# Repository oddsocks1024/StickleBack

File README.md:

# Stickleback

## Description
A clone of the First Byte Joystick Interface with audio out and pass-through for the Acorn Electron, that connects to the rear expansion connector

**Features**
* 9-pin standard Atari-type digital joystick connector
* Compatible with the First Byte Switched Joystick Interface
  * Compatible with games that include native First Byte support
  * Compatible with most keyboard only games (via FB utility)
  * Compatible with most analogue joystick games (via FB utility)
* 3.5mm Audio Out Jack (externally amplified devices only)
* Pass-through connector
* Power LED

**Compatible Joysticks**

Any DE9 (9pin) digital joystick or joypad that uses the 'Atari' single button standard. This standard was very common on many computers and
consoles of the era and was not exclusive to Atari systems. For example joysticks which claim they are compatible with Atari Systems, C64, Amiga, VIC-20,
Kempston and others should work fine.

**Incompatible Joystick Standards**

Although these joysticks standards use the same DE9 connector, they use incompatible signalling and should not be used with the Stickleback

| Incompatible Standards |
|------------------------|
| 3D0                    |
| Interface II           |
| J-PC                   |
| MSX                    |
| SEGA                   |
| Sinclair               |
| X68000                 |

## Bill of Materials

| Qty | Component                                 |
|:---:|-------------------------------------------|
| 1   | 5mm LED                                   |
| 1   | 330Ω Axial Resistor - ¼ watt (LED)        |
| 4   | 10KΩ Axial Resistors - ¼ watt             |
| 1   | 74LS138 16pin DIP                         |
| 1   | 74LS367 16pin DIP                         |
| 1   | 74LS30 14pin DIP                          |
| 1   | 10uF Radial Electrolytic Capacitor        |
| 1   | 5-pin 3.5mm Audio Jack Socket TN/T/RN/R/S |
| 1   | Male DE-9 Connector - right angled        |
| 1   | 50pin (2x25) Edge Connector               |

* IC sockets optional
* The LED resistor is nominally 330Ω but anything up to 1K is fine
* The 3.5mm jack audio socket footprint is for a 5pin TN/T/RN/R/S connector
  * If you do not care about audio, you can omit the audio socket and the 10uF capacitor entirely.
  * As the audio is mono and no switching is enabled, TN/T/RN/R are all wired together.
  * This means should be compatible with several other 3.5mm jack socket types. 

## 3D Printable Case
A 3D printable case specifically designed for this PCB is also available. STLs are included in this repo and there is also a [Thingiverse Page](https://www.thingiverse.com/thing:7089362)

* Designed to use screws as they produce a much nicer, more robust case
* 4 x 3.5mm self-tapping screws to attach the shells. Max length about 15mm

---

## Usage
The Stickleback has several modes of operation which allow the Joystick to be used with almost every Acorn Electron game.

### Native Mode
Native mode means the game has built-in support for this joystick interface and no further setup is required. This joystick interface is referred to by several names as shown
in the table

| Name                 |
|----------------------|
| First Byte Interface |
| FB Interface         |
| FCC0 Interface       |

In cases where a game requests joystick configuration values, use these values

| Parameter  | Value |
|------------|:-----:|
| Address    | FCC0  |
| Code Type  | 1     |

Examples of games with native support

| Game           |
|----------------|
| CRACK-UP       |
| FRAK!          |
| HOSTAGES       |
| RUBBLE TROUBLE |

### Keyboard Emulation Mode
This mode is used for games that have no joystick support at all. A small software routine is installed which makes the joystick emulate
key presses. See the software section for more information.

### Analogue Emulation Mode
This mode is used for games that only support Acorn's Analogue Joystick. A small software routine is installed which makes the joystick simulate
the Acorn Analogue Joystick. See the software section for more information.

### Audio
* The Stickleback provides an audio out connecting using a 3.5mm jack socket. Any audio device connected **MUST** be externally amplified
* When an external audio device is connected, the Electron's internal speaker will still produce sound. If this is not desired you can open the case and simply disconnect the internal speaker

## Software
There are some cassette tape and disc images available in the repo which contain software utilities to support the First Byte (and consequently the Stickleback) joystick interface.

### STICKLE
Available on the disc image. Test the joystick by moving a little stickleback. Very simple, only - up, down, left, right and fire.

```
   10 REM STICKLEBACK JOYSTICK TEST
   20 MODE 5
   30 VDU 23,1,0;0;0;0
   40 CLS
   50 VDU 23,240,6,12,62,127,223,255,127,62
   60 VDU 23,241,0,0,48,96,224,192,96,48
   70 X=10:Y=10
   80 COLOUR 2
   90 PRINT "STICKLEBACK JOYSTICK"
  100 PRINT TAB(X,Y);CHR$(240)+CHR$(241)
  110 F% = 0
  120 J% = ?&FCC0 AND 32
  130 IF J% <> 32 THEN F%=1
  140 J% = 31 AND ?&FCC0
  150 IF F% = 1 THEN J% = 31 - J% 
  160 IF J% > 14 AND J% < 31 THEN PRINT TAB(X,Y);"  "
  170 IF J% = 30 AND Y > 1 THEN Y = Y - 1
  180 IF J% = 29 AND Y < 29 THEN Y = Y + 1
  190 IF J% = 27 AND X > 1 THEN X = X - 1
  200 IF J% = 23 AND X < 18  THEN X = X + 1
  210 IF J% = 15 THEN SOUND 12,12,12,12
  220 GOTO 100
```

### JOYTST
Available on the disc image. The original First Byte test program which also prints the the direction values for use in BASIC
```
   10 FLAG% = 0
   20 JOY% = ?&FCC0 AND 32
   30 IF JOY% <> 32 THEN FLAG% = 1
   40 JOY% = 31 AND ?&FCC0 
   50 IF FLAG% = 1 THEN JOY% = 31 - JOY%
   60 PRINT JOY%
   70 GOTO 40

```

### JoyGame
This is the "First Byte Joystick Interface" games menu which can be loaded from the cassette or disc image. It essentially contains a list of games which are automatically "patched" to add
support for the joystick. Choose the game and then continue to load the game from cassette or disc.

| Games Menu                 |
|----------------------------|
| SNAPPER                    |
| ARCADE                     |
| FREE FALL                  |
| STARSHIP COMMAND           |
| HOPPER                     |
| MONSTERS                   |
| METEORS                    |
| MOONRAIDER                 |
| CYBERTRON MISSION          |
| SWOOP                      |
| KILLER GORILLA             | 
| CROAKER                    |
| ESCAPE FROM MOONBASE ALPHA |
| BANDITS AT 3 O'CLOCK       |
| POSITRON                   |
| ELECTRON INVADERS          | 
| GALACTIC COMMANDER         | 
| GISBURNE'S CASTLE          | 
| MR WIZ                     |
| ALIEN DROPOUT              | 
| CHUCKIE EGG                |
| KAMIKAZE                   |
| SPACE STATION ALPHA        | 
| VORTEX                     |
| DIAMOND MINE               | 
| ALIEN BREAK IN             |
| BIRDS OF PREY              | 
| ATOM SMASHER               |
| DYNABYTE POOL              | 
| BLAGGER                    |
| BUGBLASTER                 |
| LUNAR RESCUE               |
| GUARDIAN                   |
| CITY DEFENCE               |
| GALAXY WARS                |
| PENGWYN                    |
| HUNCHBACK                  |

**Cassette Loading**
 - Insert the JoyGame cassette
 - `*TAPE`
 - `CHAIN ""`
 - Choose your game from the menu
 - Insert your game cassette
 - `CHAIN ""`

**Disc Loading**
 - Insert the JoyUtils disc
  - `*DISC`
 - `CHAIN "JOYGAME"`
 - Choose your game from the menu
 - Insert your game disc
 - `*EXEC !BOOT` (do not use SHIFT+BREAK to boot)

### JoyPch
This is the "First Byte Joystick Interface" setup menu which can be loaded from the cassette or disc image. It essentially allows you to patch any game for use with the joystick. There are two analogue routines which work
with games that support analogue joysticks. The only difference between the routines is the addresses that they sit at. The last option is for keyboard emulation. You can
define the keys that the joystick will emulate then load the game.

**Cassette Loading**
 - Insert the JoyPch cassette
 - `*TAPE`
 - `CHAIN ""`
 - Choose the routine to use
 - Insert your game cassette
 - `CHAIN ""`

**Disc Loading**
 - Insert the JoyUtils disc
 - `*DISC`
 - `CHAIN "JOYPCH"`
 - Choose the routine to use
 - Insert your game disc
 - `*EXEC !BOOT` (do not use SHIFT+BREAK to boot)

## Support Me
* [My Projects](https://projects.amiga-hardware.com) - Donate on this page
* [Order the Stickleback PCB](https://www.pcbway.com/project/shareproject/StickleBack_Acorn_Electron_Joystick_Interface_Audio_Out_49529ca6.html)
* [Order the Stickleback Case](https://www.pcbway.com/project/shareproject/StickleBack_Acorn_Electron_Joystick_Interface_Case_1205cf12.html)

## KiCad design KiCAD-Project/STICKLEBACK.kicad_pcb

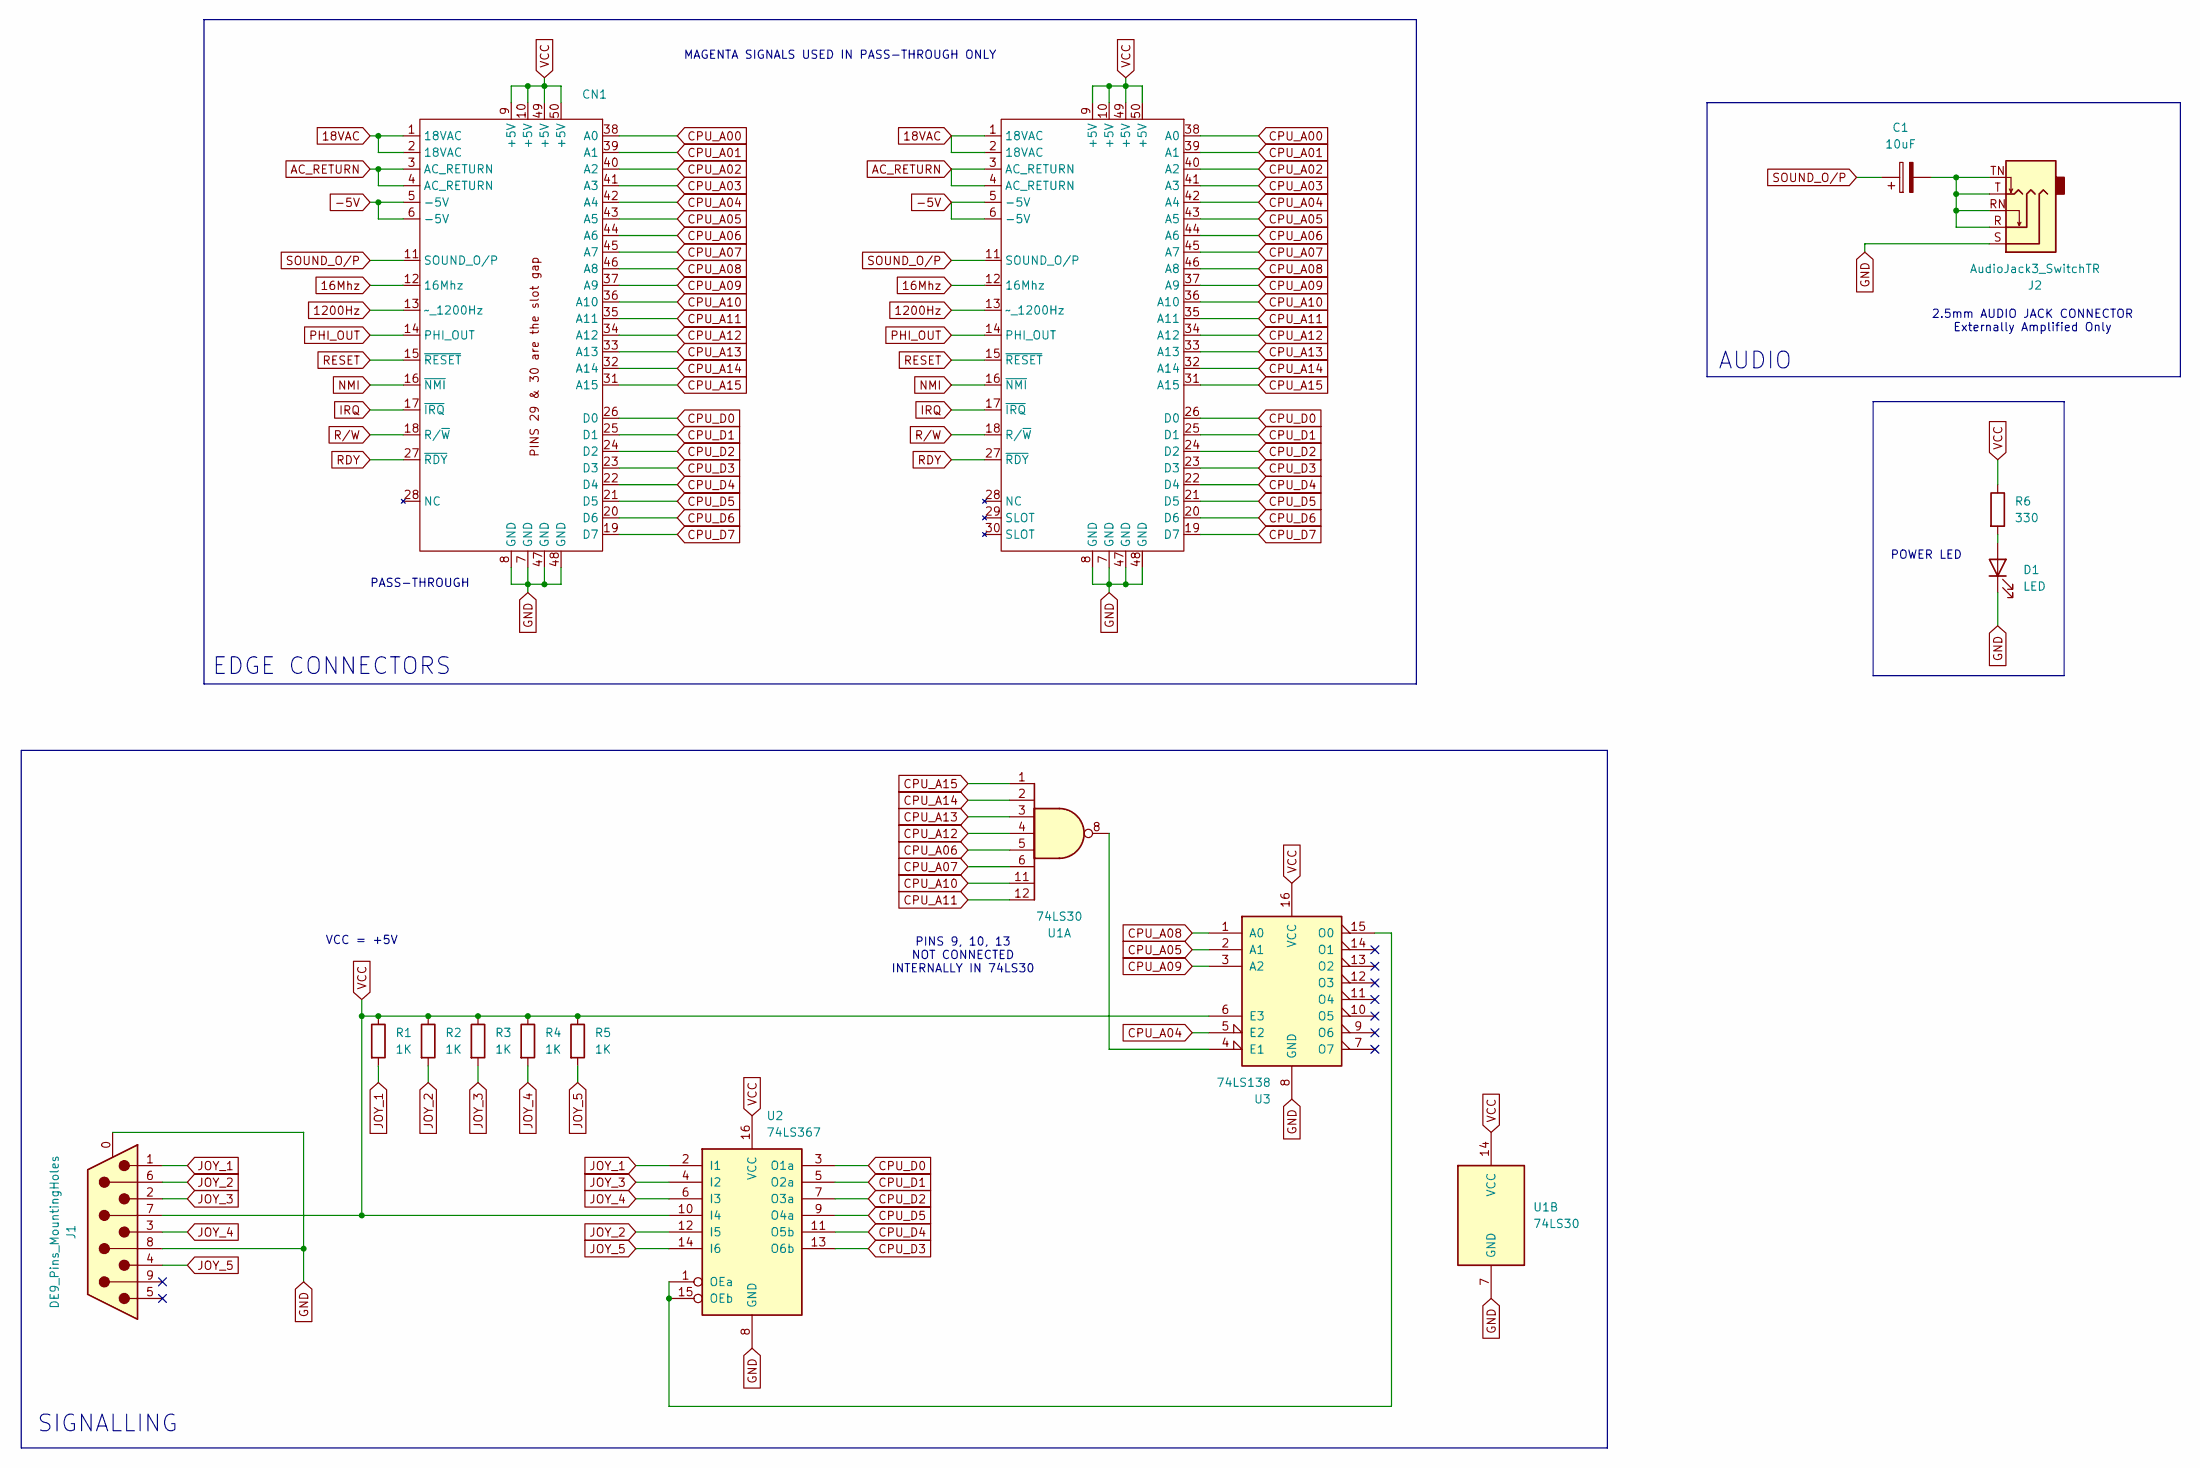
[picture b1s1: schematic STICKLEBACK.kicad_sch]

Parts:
C1: 10uF; CP_Radial_D5.0mm_P2.50mm
CN1: Acorn Electron Expansion Edge Connector
CN2: Acorn Electron TE 5530843-5 PADS
D1: LED; LED_D5.0mm
J1: DE9_Pins_MountingHoles; DSUB-9_Pins_Horizontal_P2.77x2.84mm_EdgePinOffset14.56mm_Ho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
J2: AudioJack3_SwitchTR; Jack_3.5mm_CUI_SJ1-3525N_Horizontal
R1, R2, R3, R4, R5: 1K; R_Axial_DIN0207_L6.3mm_D2.5mm_P10.16mm_Horizontal
R6: 330; R_Axial_DIN0207_L6.3mm_D2.5mm_P10.16mm_Horizontal
U1: 74LS30; DIP-14_W7.62mm_Socket
U2: 74LS367; DIP-16_W7.62mm_Socket
U3: 74LS138; DIP-16_W7.62mm_Socket

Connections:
16Mhz: CN1.12 (16Mhz), CN2.12 (16Mhz)
18VAC: CN1.1 (18VAC), CN1.2 (18VAC), CN2.1 (18VAC), CN2.2 (18VAC)
1200Hz: CN1.13 (~_1200Hz), CN2.13 (~_1200Hz)
-5V: CN1.5 (-5V), CN1.6 (-5V), CN2.5 (-5V), CN2.6 (-5V)
AC_RETURN: CN1.3 (AC_RETURN), CN1.4 (AC_RETURN), CN2.3 (AC_RETURN), CN2.4 (AC_RETURN)
CPU_A00: CN1.38 (A0), CN2.38 (A0)
CPU_A01: CN1.39 (A1), CN2.39 (A1)
CPU_A02: CN1.40 (A2), CN2.40 (A2)
CPU_A03: CN1.41 (A3), CN2.41 (A3)
CPU_A04: CN1.42 (A4), CN2.42 (A4), U3.5 (E2)
CPU_A05: CN1.43 (A5), CN2.43 (A5), U3.2 (A1)
CPU_A06: CN1.44 (A6), CN2.44 (A6), U1.5
CPU_A07: CN1.45 (A7), CN2.45 (A7), U1.6
CPU_A08: CN1.46 (A8), CN2.46 (A8), U3.1 (A0)
CPU_A09: CN1.37 (A9), CN2.37 (A9), U3.3 (A2)
CPU_A10: CN1.36 (A10), CN2.36 (A10), U1.11
CPU_A11: CN1.35 (A11), CN2.35 (A11), U1.12
CPU_A12: CN1.34 (A12), CN2.34 (A12), U1.4
CPU_A13: CN1.33 (A13), CN2.33 (A13), U1.3
CPU_A14: CN1.32 (A14), CN2.32 (A14), U1.2
CPU_A15: CN1.31 (A15), CN2.31 (A15), U1.1
CPU_D0: CN1.26 (D0), CN2.26 (D0), U2.3 (O1a)
CPU_D1: CN1.25 (D1), CN2.25 (D1), U2.5 (O2a)
CPU_D2: CN1.24 (D2), CN2.24 (D2), U2.7 (O3a)
CPU_D3: CN1.23 (D3), CN2.23 (D3), U2.13 (O6b)
CPU_D4: CN1.22 (D4), CN2.22 (D4), U2.11 (O5b)
CPU_D5: CN1.21 (D5), CN2.21 (D5), U2.9 (O4a)
CPU_D6: CN1.20 (D6), CN2.20 (D6)
CPU_D7: CN1.19 (D7), CN2.19 (D7)
GND: CN1.7 (GND), CN1.8 (GND), CN1.47 (GND), CN1.48 (GND), CN2.7 (GND), CN2.8 (GND), CN2.47 (GND), CN2.48 (GND), D1.1 (K), J1.0 (PAD), J1.8, J2.S, U1.7 (GND), U2.8 (GND), U3.8 (GND)
IRQ: CN1.17 (~IRQ), CN2.17 (~IRQ)
JOY_1: J1.1, R1.2, U2.2 (I1)
JOY_2: J1.6, R2.2, U2.12 (I5)
JOY_3: J1.2, R3.2, U2.4 (I2)
JOY_4: J1.3, R4.2, U2.6 (I3)
JOY_5: J1.4, R5.2, U2.14 (I6)
NMI: CN1.16 (~NMI), CN2.16 (~NMI)
unnamed: C1.2, J2.R, J2.RN, J2.T, J2.TN
unnamed: D1.2 (A), R6.2
unnamed: U2.1 (OEa), U2.15 (OEb), U3.15 (O0)
unnamed: U1.8, U3.4 (E1)
PHI_OUT: CN1.14 (PHI_OUT), CN2.14 (PHI_OUT)
RDY: CN1.27 (~RDY), CN2.27 (~RDY)
RESET: CN1.15 (~RESET), CN2.15 (~RESET)
R/W: CN1.18 (R/~W), CN2.18 (R/~W)
SOUND_O/P: C1.1, CN1.11 (SOUND_O/P), CN2.11 (SOUND_O/P)
VCC: CN1.9 (+5V), CN1.10 (+5V), CN1.49 (+5V), CN1.50 (+5V), CN2.9 (+5V), CN2.10 (+5V), CN2.49 (+5V), CN2.50 (+5V), J1.7, R1.1, R2.1, R3.1, R4.1, R5.1, R6.1, U1.14 (VCC), U2.10 (I4), U2.16 (VCC), U3.6 (E3), U3.16 (VCC)

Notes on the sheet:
2.5mm AUDIO JACK CONNECTOR Externally Amplified Only
MAGENTA SIGNALS USED IN PASS-THROUGH ONLY
VCC = +5V
EDGE CONNECTORS
POWER LED
AUDIO
PINS 9, 10, 13 NOT CONNECTED INTERNALLY IN 74LS30
PASS-THROUGH
SIGNALLING

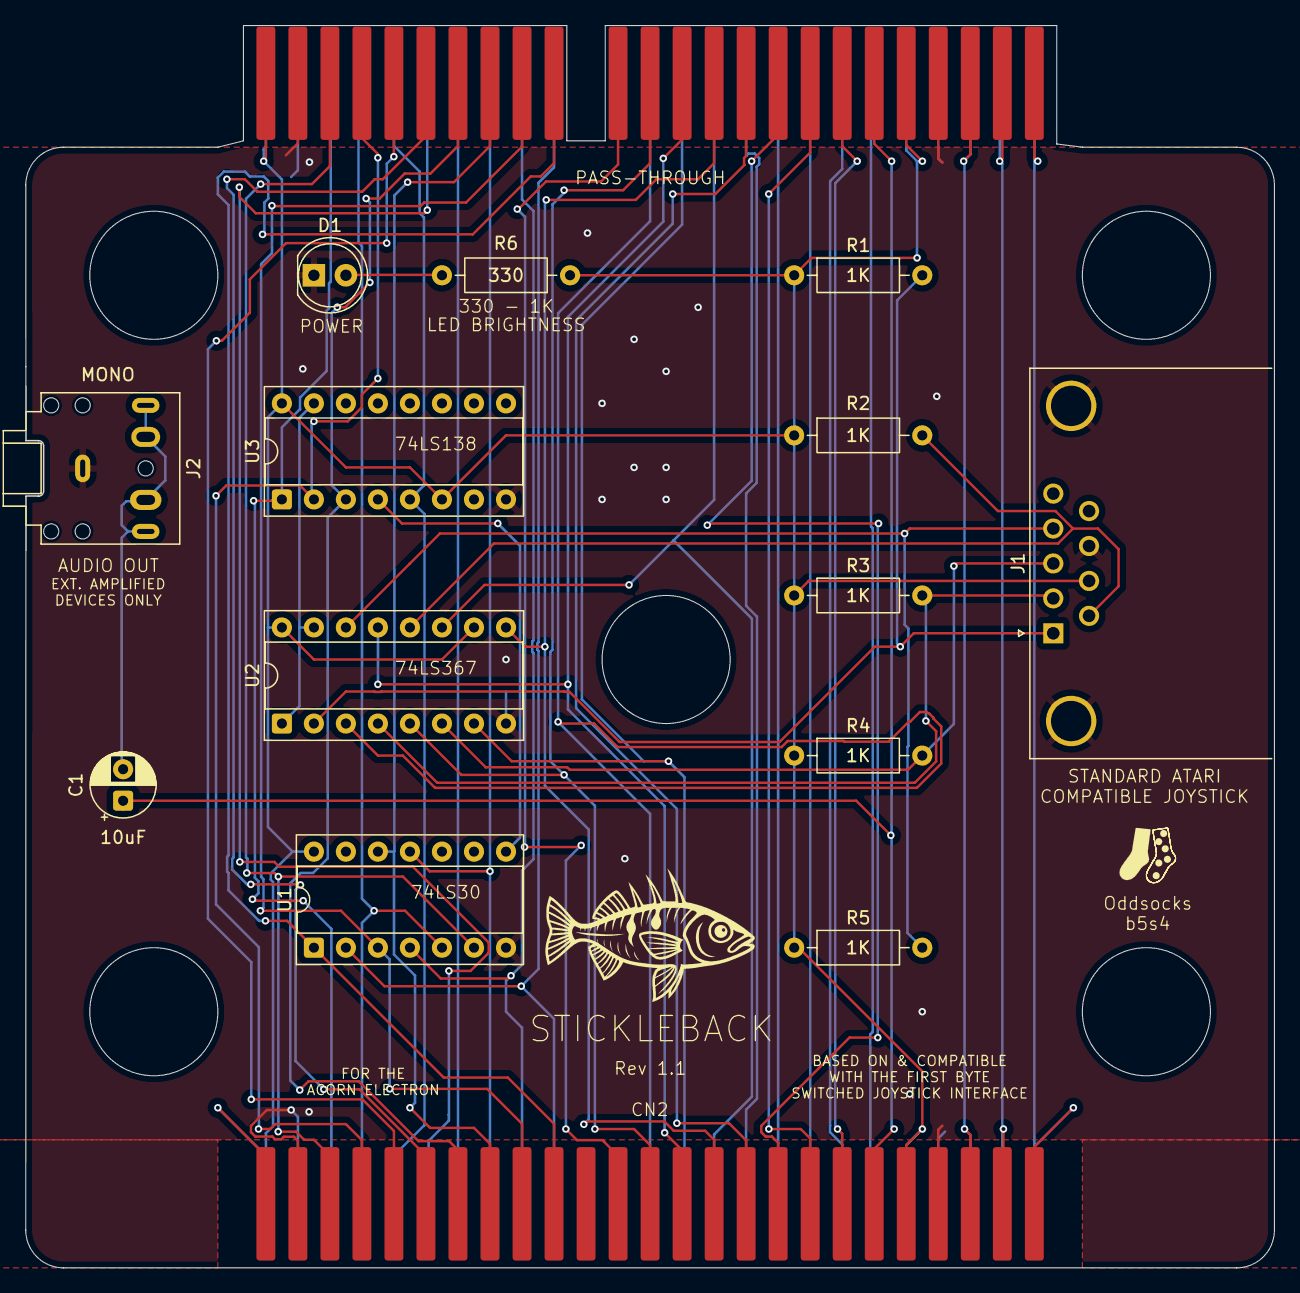
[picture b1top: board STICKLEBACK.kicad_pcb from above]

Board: 2 copper layers, 99.1 x 98.6 mm, 15 parts (0 on the bottom side), 47 nets.

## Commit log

2025-09-05 Added an additional image
2025-09-06 Updated PCB link
2025-10-04 Fix case PCB URL
2025-10-06 Added STICKLE test and update SSD
2025-11-09 Added gerbers
2025-11-30 Add license file
2025-11-30 Added PDF schematics
